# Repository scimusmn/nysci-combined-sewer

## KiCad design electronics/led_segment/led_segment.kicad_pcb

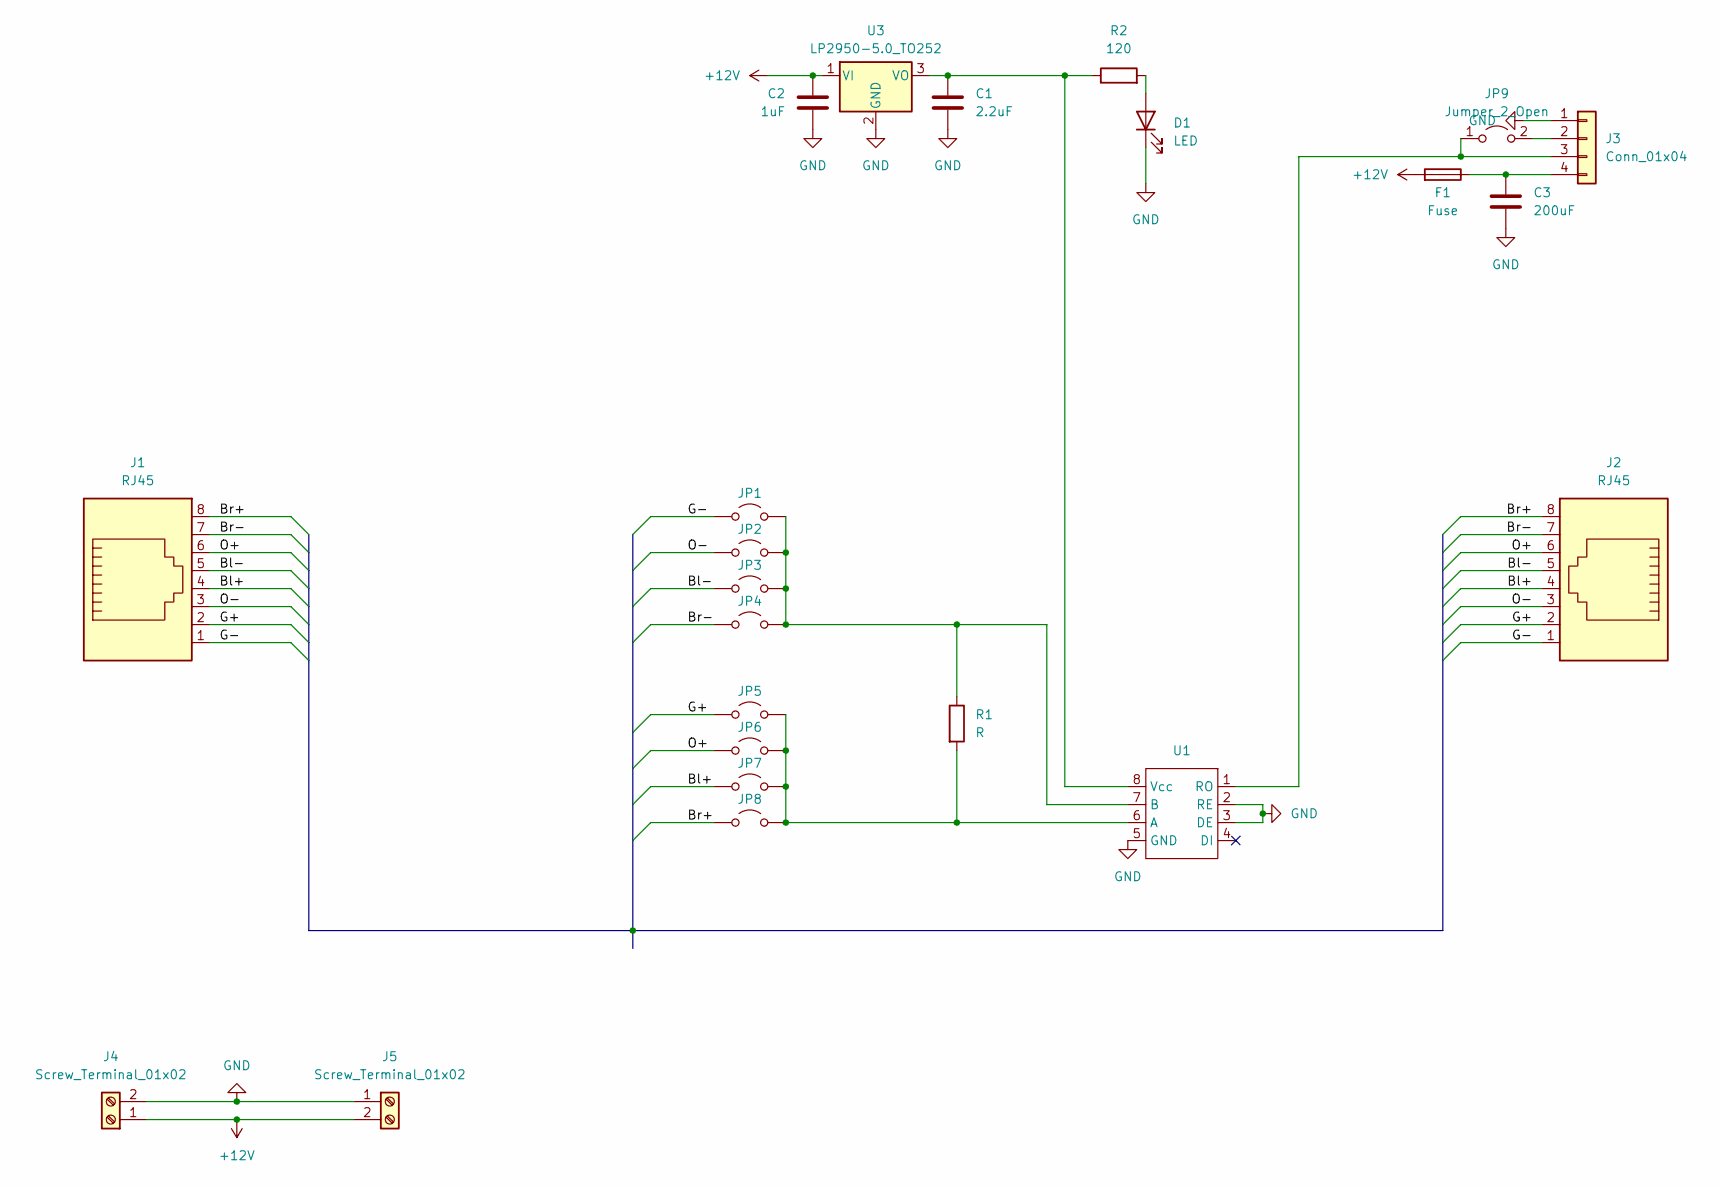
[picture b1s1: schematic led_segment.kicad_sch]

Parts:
C1: 2.2uF; C_0805_2012Metric; LCSC C377773
C2: 1uF; C_0805_2012Metric; LCSC C28323
C3: 200uF; CP_EIA-7361-38_AVX-V; LCSC TAJV227M016RNJ
D1: LED; LED_D3.0mm
F1: Fuse; 3549-2
J1, J2: RJ45; RJ45_Ninigi_GE; LCSC C708636
J3: Conn_01x04; KK-1x04_right
J4, J5: Screw_Terminal_01x02; P-2604-1102_1
JP1, JP2, JP3, JP4, JP5, JP6, JP7, JP8, JP9: Jumper_2_Open; SolderJumper-2_P1.3mm_Open_Pad1.0x1.5mm
R1: R; R_1206_3216Metric
R2: 120; R_1206_3216Metric
U1: SOIC-8_3.9x4.9mm_P1.27mm; LCSC C7422579
U3: LP2950-5.0_TO252; TO-252-2; LCSC C130186

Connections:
+12V: C2.1, F1.2, J4.1, J5.2, U3.1 (VI)
/Bl+: J1.4, J2.4, JP7.1 (A)
/Bl-: J1.5, J2.5, JP3.1 (A)
/Br+: J1.8, J2.8, JP8.1 (A)
/Br-: J1.7, J2.7, JP4.1 (A)
/G+: J1.2, J2.2, JP5.1 (A)
/G-: J1.1, J2.1, JP1.1 (A)
/O+: J1.6, J2.6, JP6.1 (A)
/O-: J1.3, J2.3, JP2.1 (A)
GND: C1.2, C2.2, C3.2, D1.1 (K), J3.1, J4.2, J5.1, U1.2 (RE), U1.3 (DE), U1.5 (GND), U3.2 (GND)
unnamed: D1.2 (A), R2.2
unnamed: J3.2, JP9.2 (B)
unnamed: J3.3, JP9.1 (A), U1.1 (RO)
unnamed: C3.1, F1.1, J3.4
unnamed: JP1.2 (B), JP2.2 (B), JP3.2 (B), JP4.2 (B), R1.1, U1.7 (B)
unnamed: JP5.2 (B), JP6.2 (B), JP7.2 (B), JP8.2 (B), R1.2, U1.6 (A)
unnamed: C1.1, R2.1, U1.8 (Vcc), U3.3 (VO)

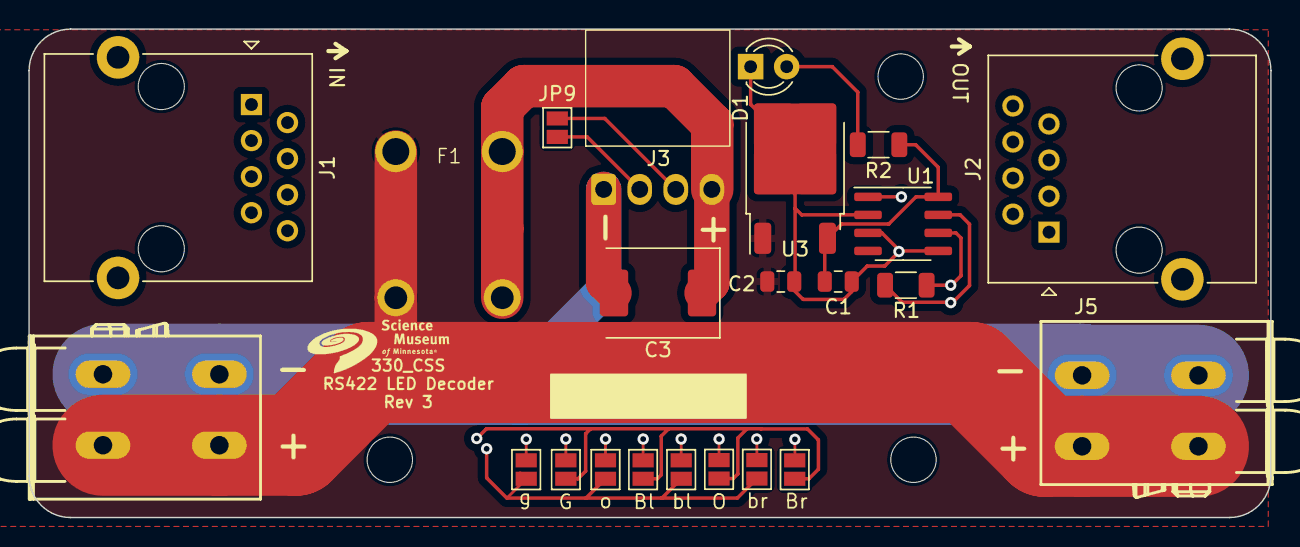
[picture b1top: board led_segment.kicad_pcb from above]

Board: 4 copper layers, 87.5 x 34.4 mm, 23 parts (0 on the bottom side), 17 nets.

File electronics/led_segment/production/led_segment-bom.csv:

Comment,Designator,Footprint,LCSC
"2.2uF","C1","Capacitor_SMD:C_0805_2012Metric","C377773"
"1uF","C2","Capacitor_SMD:C_0805_2012Metric","C28323"
"200uF","C3","Capacitor_Tantalum_SMD:CP_EIA-7361-38_AVX-V","TAJV227M016RNJ"
"Fuse","F1","Library:3549-2",""
"RJ45","J1,J2","SMM:RC01516","C708636"
"Conn_01x04","J3","SMM:KK-1x04_right",""
"Screw_Terminal_01x02","J4,J5","2604-1102:P-2604-1102_1",""
"~","U1","Package_SO:SOIC-8_3.9x4.9mm_P1.27mm","C7422579"
"LP2950-5.0_TO252","U3","Package_TO_SOT_SMD:TO-252-2","C130186"

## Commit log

2024-08-13 re-implement jumpers
2024-08-13 add basic pipes mechanism
2024-08-14 consolidate self and input flows
2024-08-14 fix inserting NO_FLOW flows
2024-08-14 implement can transmission of levels
2024-08-15 finalize css model demo
2024-08-15 begin mapping UM segment
2024-08-15 map UM segment
2024-08-15 map lm segment
2024-08-15 map bottom segment
2024-08-15 get nice flow overlap
2024-08-16 add address-finder.ino
2024-08-16 implement rain
2024-08-16 add rain switch
2024-08-16 add basic demo code README
2024-08-16 add comments to messages.h
2024-08-20 update graph & flow color length
2024-08-20 initial working wall integration
2024-08-21 put up wall
2024-12-03 sketch out demo2 code
2024-12-03 update icons
2024-12-06 get peer review on rev.3 of boards
2024-12-10 confirm layout of updates
2025-01-08 add python camera script
2025-01-08 add conda environment and cl/fl controllers
2025-01-13 add finder.py
2025-01-13 move finder.py to address-query
2025-01-13 fix nullptr bug in flow.cpp
2025-01-13 remove types in demo2-controller-fl
2025-01-13 use static memory for flows and input pipes
2025-01-13 remove superfluous debug printing
2025-01-14 Update pipes.cpp fl fixed one pixel too far
2025-01-14 Update buttons to correct pins
2025-01-14 Update demo2-icons.ino
    defined processInputLevels()
2025-01-15 Bug fix FL(Building 1)
2025-01-18 fix switch interrupts
2025-01-18 fix pins
2025-01-18 add blink signal to fl boot
2025-01-18 add rain animation
2025-01-18 fix speed randomization
2025-01-18 increase rain speed flexibility
2025-01-21 Fix reverse bug
2025-01-21 implement constant flows
2025-01-21 pushin cl
2025-01-21 update flow.*
2025-01-21 remove flowtype reference in demo2-controller-cl
2025-01-21 move pipe definition macros into flow.h
2025-01-21 remove flowtypes from startFlow calls
2025-01-21 CL all done
2025-01-22 merge
2025-01-22 add controllers folder
2025-01-22 fix shorts
2025-01-22 flow changes
2025-01-22 do not track local changes to template files
2025-01-22 fix update-all.bat
2025-01-22 fix unbounded flow growth
2025-01-22 remove tryUpdateFlows call
2025-01-22 set initial flow values to zero
2025-01-22 adjust code to new direction
2025-01-23 begin adding can pipe output
2025-01-23 change leader color to 00ff80
2025-01-24 implement virtual pipes
2025-01-24 remove VPIPE macro and bundle createPipes arguments into single struct
2025-01-24 implement cross-building overflow
2025-01-25 Adjust floor to fit in with receiving inputs
2025-01-27 make sure pipe addresses match the standard we wanted
2025-01-27 redo
2025-01-27 Cross building pipes mapped
2025-01-28 refactor: separate input, output, and rendering in pipe
2025-01-28 implement cross-can overflow
2025-01-28 tranfer icon update to all icons
2025-01-28 fix 0-input draining bug
2025-01-28 create timeout.*
2025-01-28 fix errors in timeout.*
2025-01-28 add flow activation levels and fix can bus communication bug
2025-01-28 get pipe flows to match icon levels
2025-01-28 update other buildings
2025-01-28 change default flow level to 1
2025-01-29 fine tune timing on buttons and icons
2025-01-29 begin implementing overflow pipe
2025-01-29 add multiple renderers per pipe
2025-01-29 fix function def
2025-01-29 poonami adjustment
2025-01-29 begin poonami implementation
2025-01-29 fix typo
2025-01-29 implement flowcount-based poonami event
2025-01-29 implement cso/poonami events based on user input timing
2025-01-30 fine tune events
2025-01-31 make it flash
2025-01-31 add extraProcessInputLevels pointer
2025-01-31 implement level holding on controller-floor
2025-01-31 make the switches control the color swap
2025-01-31 darn those capitalization errors
2025-01-31 fix merge conflict
2025-01-31 Microsoft Notepad for the win!
2025-01-31 implement color swap message sending/processing
2025-01-31 add overflow clock pulse
2025-01-31 adjust switches code to send overflow color timeouts
2025-01-31 add dummy fn definitions
2025-01-31 use overflowColor
2025-01-31 final code, needs clean up and adjustments based on Nysci
2025-03-11 troubleshooting on site
2025-03-11 update template
2025-03-18 updated final
